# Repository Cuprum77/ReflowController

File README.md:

# Reflow Controller

This is my own take at building my own reflow oven. This repo will contain all the documentation, code and hardware design files.

## Oven

As there are no easily available small oven here in Norway for a reasonable price, I settled on the [Point PMO16BL](https://www.power.no/kjoekkenmaskiner/kjoekkenapparater/miniovn-og-frittstaaende-platetopp/point-pmo16bl-miniovn/p-1136808/) from Power, a Norwegian electronics store. It's a 16L oven with a max temperature of 230°C. However I do believe we can get it to go higher than that.

Through coupons and discounts I managed to get one brand new from a store for as little as 291 NOK, which as of now (2023-05-14) is about 20.54 USD.

## Controller

The controller itself is designed to be as simple as possible and have to navigate around the still ongoing chip shortage. It features an RP2040 microcontroller, a 1.28" circular LCD display, a button, and the option for a rotary encoder as well as up to 3 thermocouple inputs and 3 relays for controlling the oven.

However, it is not capable of receiving the thermocouples straight in, even though it would have been more practical. This is due to the chips chosen were not available on their own, but only as a breakout board. So to save time and effort, I decided against simply moving the chips over to a main board, and instead just use the breakout boards as is. An advantage of this approach, is the potential for a solderless experience if more thermocouples are needed in the future.

The controller will also feature an onboard EEPROM for storing the heat profiles and settings as well as a USB-C connector for programming. The board can be powered directly from mains through a large plug in connector.

## Software

## License
This project is licensed under the CERN Open Hardware Licence v2 - Strong Reciprocity (CERN-OHL-S-2.0). See [LICENSE](./LICENSE) for more information.

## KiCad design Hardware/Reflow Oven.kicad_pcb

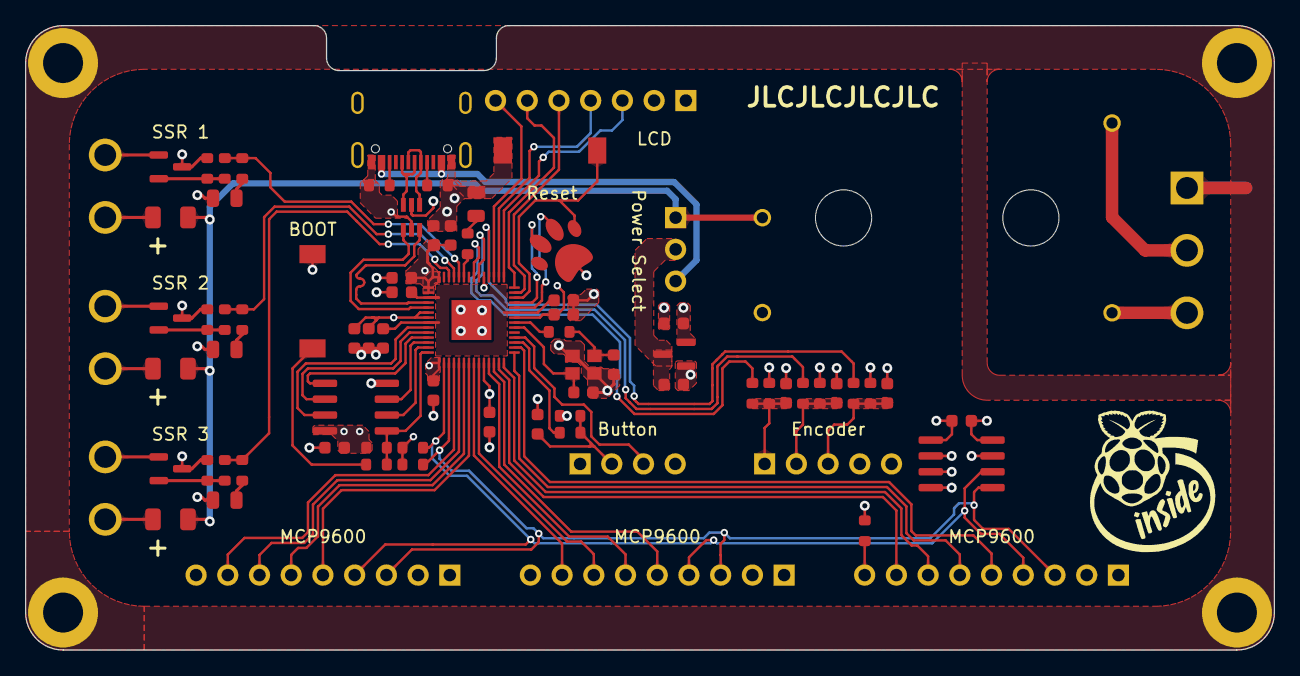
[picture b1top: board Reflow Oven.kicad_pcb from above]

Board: 4 copper layers, 100.0 x 50.0 mm, 83 parts (0 on the bottom side), 74 nets.

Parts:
C1, C2, C3, C4: 10n; C_0603_1608Metric
C5, C8, C10, C11, C12, C13, C14, C16, C17, C18, C20: 100n; C_0603_1608Metric
C6, C7: 8p; C_0603_1608Metric
C9, C19: 1u; C_0603_1608Metric
C15: 10u; C_0603_1608Metric
C21: 2u2; C_0603_1608Metric
D1, D2, D3, D4: Red; D_0805_2012Metric
F1, F2, F3: Fuse; Fuse_1206_3216Metric
H1, H2, H3, H4: M3; MountingHole_3.2mm_M3_DIN965_Pad
IC1: MCP1792T; SOT-23
J1: SW; PinHeader_1x04_P2.54mm_Vertical
J2: ENC; PinHeader_1x05_P2.54mm_Vertical
J3, J4, J5: Adafruit 4101; PinHeader_1x09_P2.54mm_Vertical
J6: GC9A01 1.28" TFT; PinHeader_1x07_P2.54mm_Vertical
J7: 2350513-3
J8, J9, J10: 2350513-2
J11: USB4110-GF-A_REVB; USB_C_Receptacle_GCT_USB4105-xx-A_16P_TopMnt_Horizontal
J12: POW_SEL; PinHeader_1x03_P2.54mm_Vertical
J13: PawPad_SWD; pawpad
P1: IRM015
Q1, Q2, Q3: IRLML2060; SOT-23
R1, R23, R24: 2k2; R_0603_1608Metric
R2, R3, R4, R5, R6, R7, R8, R9, R14, R17, R20: 10k; R_0603_1608Metric
R10, R11: 5k1; R_0603_1608Metric
R12, R15, R18, R26: 270; R_0603_1608Metric
R13, R16, R19: 100; R_0603_1608Metric
R21, R22: DNF; R_0603_1608Metric
R25: 1k; R_0603_1608Metric
SW1, SW2: DNF; PTS636 SM25J SMTR LFS
U1: USBUF02W6; SOT65P210X110-6N
U2: W25Q16JV; SOIC-8_3.9x4.9mm_P1.27mm
U3: FT24C04A; SOIC-8_3.9x4.9mm_P1.27mm
U4: RP2040; QFN-56-1EP_7x7mm_P0.4mm_EP3.2x3.2mm
Y1: 12MHz; Crystal_SMD_2520-4Pin_2.5x2.0mm

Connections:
+1V1: C5.1, C8.1, C9.1, U4.23 (DVDD), U4.45 (VREG_VOUT), U4.50 (DVDD)
+3V3: C10.1, C11.1, C12.1, C13.1, C14.1, C16.1, C17.1, C18.1, C19.1, C20.1, C21.1, IC1.2, J1.1, J2.4, J3.1, J4.1, J5.1, J6.1, R2.1, R3.1, R5.1, R8.1, R22.2, R23.1, R24.1, U1.5 (3V3), U2.8 (VCC), U3.8 (VCC), U4.1 (IOVDD), U4.10 (IOVDD), U4.22 (IOVDD), U4.33 (IOVDD), U4.42 (IOVDD), U4.43 (ADC_AVDD), U4.44 (VREG_IN), U4.48 (USB_VDD), U4.49 (IOVDD)
+5V: F1.1, F2.1, F3.1, J12.1, P1.1 (V+)
/ALARM1A: J3.5, U4.7 (GPIO5)
/ALARM1B: J4.5, U4.16 (GPIO13)
/ALARM1C: J5.5, U4.12 (GPIO9)
/ALARM2A: J3.6, U4.6 (GPIO4)
/ALARM2B: J4.6, U4.15 (GPIO12)
/ALARM2C: J5.6, U4.11 (GPIO8)
/ALARM3A: J3.7, U4.5 (GPIO3)
/ALARM3B: J4.7, U4.14 (GPIO11)
/ALARM3C: J5.7, U4.9 (GPIO7)
/ALARM4A: J3.8, U4.4 (GPIO2)
/ALARM4B: J4.8, U4.13 (GPIO10)
/ALARM4C: J5.8, U4.8 (GPIO6)
/Button Filter/SW_OUT: R9.1, U4.17 (GPIO14)
/ENC_A: C1.1, J2.1, R2.2, R4.2
/ENC_B: C2.1, J2.2, R3.2, R6.2
/ENC_Filter/ENC_A_OUT: R4.1, U4.35 (GPIO23)
/ENC_Filter/ENC_B_OUT: R6.1, U4.34 (GPIO22)
/ENC_Filter/ENC_SW_OUT: R7.1, U4.32 (GPIO21)
/ENC_SW: C3.1, J2.3, R5.2, R7.2
/LCD_CS: J6.6, U4.28 (GPIO17)
/LCD_D/C: J6.5, U4.27 (GPIO16)
/LCD_MOSI: J6.4, U4.30 (GPIO19)
/LCD_RST: J6.7, U4.31 (GPIO20)
/LCD_SCK: J6.3, U4.29 (GPIO18)
/Live: J7.2, P1.4 (L)
/MOSFET_1: R12.1, R13.1, U4.40 (GPIO28_ADC2)
/MOSFET_2: R15.1, R16.1, U4.38 (GPIO26_ADC0)
/MOSFET_3: R18.1, R19.1, U4.39 (GPIO27_ADC1)
/MOSFETs/SSR_1: J8.2, Q1.1 (D)
/MOSFETs/SSR_1_COM: F1.2, J8.1
/MOSFETs/SSR_2: J9.2, Q2.1 (D)
/MOSFETs/SSR_2_COM: F2.2, J9.1
/MOSFETs/SSR_3: J10.2, Q3.1 (D)
/MOSFETs/SSR_3_COM: F3.2, J10.1
/Microcontroller Alarm/LED_ACTIVE: R26.2, U4.37 (GPIO25)
/Microcontroller Alarm/QSPI_SCLK: U2.6 (CLK), U4.52 (QSPI_SCLK)
/Microcontroller Alarm/QSPI_SD0: U2.5 (DI(IO0)), U4.53 (QSPI_SD0)
/Microcontroller Alarm/QSPI_SD1: U2.2 (DO(IO1)), U4.55 (QSPI_SD1)
/Microcontroller Alarm/QSPI_SD2: U2.3 (IO2), U4.54 (QSPI_SD2)
/Microcontroller Alarm/QSPI_SD3: U2.7 (IO3), U4.51 (QSPI_SD3)
/Microcontroller Alarm/QSPI_SS: R21.2, R22.1, U2.1 (~CS), U4.56 (QSPI_SS)
/Microcontroller Alarm/RST: J13.4 (NRST), SW2.2, U4.26 (RUN)
/Microcontroller Alarm/SWCLK: J13.3 (SWCLK), U4.24 (SWCLK)
/Microcontroller Alarm/SWD: J13.2 (SWDIO), U4.25 (SWD)
/Microcontroller Alarm/SW_LED: J1.3, U4.18 (GPIO15)
/Microcontroller Alarm/USB_D+: U1.1 (D+), U4.47 (USB_DP)
/Microcontroller Alarm/USB_D-: U1.3 (D-), U4.46 (USB_DM)
/Microcontroller Alarm/XIN: C6.2, U4.20 (XIN), Y1.1
/Microcontroller Alarm/XOUT: R25.1, U4.21 (XOUT)
/Neutral: J7.3, P1.3 (N)
/SCL: J3.3, J4.3, J5.3, R24.2, U3.5 (SDA), U4.3 (GPIO1)
/SDA: J3.4, J4.4, J5.4, R23.2, U3.6 (SCL), U4.2 (GPIO0)
/SW: C4.1, J1.2, R8.2, R9.2
/USB/USB_PRE_D+: J11.A6 (D+), J11.B6 (D+), U1.6 (D+)
/USB/USB_PRE_D-: J11.A7 (D-), J11.B7 (D-), U1.4 (D-)
Earth: H1.1, H2.1, H3.1, H4.1, J7.1
GND: C1.2, C2.2, C3.2, C4.2, C5.2, C6.1, C7.1, C8.2, C9.2, C10.2, C11.2, C12.2, C13.2, C14.2, C15.2, C16.2, C17.2, C18.2, C19.2, C20.2, C21.2, D1.1 (K), D2.1 (K), D3.1 (K), D4.1 (K), IC1.1, J1.4, J2.5, J3.2, J4.2, J5.2, J5.9, J6.2, J11.A1/B12 (GND), J11.B1/A12 (GND), J13.5 (GND), P1.2 (V-), Q1.3 (S), Q2.3 (S), Q3.3 (S), R1.1, R10.2, R11.2, R14.2, R17.2, R20.2, SW1.1, SW2.1, U1.2 (Grd), U2.4 (GND), U3.1 (A0), U3.2 (A1), U3.3 (A3), U3.4 (GND), U3.7 (WP), U4.57 (GND), Y1.2, Y1.4
unnamed: C7.2, R25.2, Y1.3
unnamed: D1.2 (A), R12.2
unnamed: D2.2 (A), R15.2
unnamed: D3.2 (A), R18.2
unnamed: D4.2 (A), R26.1
unnamed: J4.9, R1.2
unnamed: J11.A5 (CC1), R10.1
unnamed: J11.B5 (CC2), R11.1
unnamed: C15.1, IC1.3, J12.2
unnamed: Q1.2 (G), R13.2, R14.1
unnamed: Q2.2 (G), R16.2, R17.1
unnamed: Q3.2 (G), R19.2, R20.1
unnamed: R21.1, SW1.2
VBUS: J11.A4/B9 (VBUS), J11.B4/A9 (VBUS), J12.3

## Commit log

2023-05-12 loicense
2023-05-12 basic firmware setup
2023-05-13 minor work left on rev1
2023-05-13 added models
2023-05-13 minor tweaks
2023-05-13 render
2023-05-13 pin definitions
2023-05-13 fixing potential acid traps
2023-05-13 refactor
2023-05-14 fixed typo
2023-05-14 changed i2c pins to match current development
2023-05-14 added the memory library
2023-05-14 created a library for interfacing with MCP9600
2023-05-14 updated main in accordance with former commits
2023-05-14 basic readme
2023-05-14 some additional changes
2023-05-14 removed gerber for now
2023-05-14 minor changes
2023-05-16 i dont know what im doing
2023-05-18 i dont know what im doing wrong
2023-05-19 moved display driver to its own repo
2023-05-19 small changes
2023-05-23 functional prototype
2023-05-23 update submodule in use
2023-05-26 updated to include new picogfx changes
2023-06-07 small pcb improvements
2023-06-07 2 layer variant
2023-06-13 redid 2 layer, thanks git
2023-06-13 ordered from aisler
2023-06-13 solder mask missing!
2023-06-13 added date
2023-06-20 added missing teardrops
2023-06-20 minor fixes
2023-07-04 added BOM
2023-07-25 updated to the latest gfx version
2023-08-15 updated the schematic with the value for R21
2023-08-15 cleaned up the cmake and added new files
2023-08-15 added new defines, added new includes
2023-08-15 start of the error handling code
2023-08-15 seperated the menu system into its own file
2023-08-15 seperated the oven code into its own file
2023-08-15 rotary encoder class placeholder
2023-08-15 minor cleanup
2023-08-15 updated picogfx to latest version
2023-08-15 added the button library from the PD project
2023-08-15 removed menu and oven code from main
2023-08-15 moved heatmap to its own file
2023-08-15 cleanup, made some variables global
2023-08-15 cleanup and fixing race conditions
2023-08-17 fixed the oven problem
2024-01-09 old updates i forgot to push
2024-01-09 removed ibom from linguist
2024-01-09 image of a repair
2024-01-09 added a basic plotter to see temperature real time
